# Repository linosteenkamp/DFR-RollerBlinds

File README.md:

# DFR-RollerBlinds

**ESP32-C6 stepper-driven Zigbee-router roller blind controller**

> *Photo placeholder — installed enclosure + motor + roller tube, to be added
> after bench verification.*

A Seeed XIAO ESP32C6 that drives a bipolar stepper (through a BIGTREETECH
TMC2209 and a 3D-printed 1:15 reduction) to raise and lower a roller blind,
in near silence thanks to the driver's StealthChop2 chopping, and presents a
standard **Window Covering** device (cluster 0x0102) to zigbee2mqtt / Home
Assistant. It joins the mesh as a **Zigbee Router** — mains-powered,
always-on, relays traffic and extends network range. A 3-key membrane keypad
(Up / Down / Fn) gives full local control and hosts a guided calibration
flow; firmware updates are delivered over the air through zigbee2mqtt.

## Features

- **Window Covering cluster (0x0102)** — full open/close, stop, and
  go-to-percentage, with live lift-position reporting during moves
- **Local keypad control** — tap for full travel, hold to jog, works even
  before calibration or with Zigbee down
- **Guided calibration** — hold Fn ~3 s, jog to the two limits, done; LED
  feedback at every step
- **Position Unknown recovery** — a power cut mid-move is detected and
  recovered with a lightweight one-mark Re-home instead of full recalibration
- **Motor Reversed** — per-unit installer setting (keypad chord or z2m),
  correcting for front-roll vs back-roll installs
- **Zigbee Router** — always-on radio, relays traffic and extends the mesh;
  built on the shared `esp-zb-common` library
- **Zigbee OTA** — CI-built images delivered through zigbee2mqtt with
  dual-slot bootloader rollback
- **Host-testable core** — position math, ramp planning, and keypad gesture
  classification are pure-C modules with a `native` unit-test suite

## Getting started

```bash
# Build & flash
pio run -e seeed_xiao_esp32c6_zigbee -t upload -t monitor

# Host unit tests
pio test -e native
```

Pairing, calibration, and OTA setup are in
[DEVELOPER_GUIDE.md](DEVELOPER_GUIDE.md).

> **Fitting a unit to a blind?** Follow the
> [per-blind install checklist](HARDWARE.md#installing-a-unit-per-blind-checklist).
> The fleet uses **two different motors**, and each needs its own Vref *and* its
> own motor cable — the cables are not interchangeable, and mismatching either
> one produces a stall that looks like a firmware or speed problem.

## Documentation

- **[HARDWARE.md](HARDWARE.md)** — BOM, power chain, TMC2209 wiring, Vref
  procedure, keypad/LED wiring, direction check, and the
  [per-blind install checklist](HARDWARE.md#installing-a-unit-per-blind-checklist)
- **[DEVELOPER_GUIDE.md](DEVELOPER_GUIDE.md)** — pairing, calibration
  walkthrough, bench checklist, OTA release flow
- **[CLAUDE.md](CLAUDE.md)** — architecture, module table, concurrency rule
- **[PARTITIONS.md](PARTITIONS.md)** — flash partition layout (dual-OTA)
- **[docs/superpowers/specs/2026-07-18-roller-blinds-design.md](docs/superpowers/specs/2026-07-18-roller-blinds-design.md)** — full design spec

## License

Provided as-is for educational and development purposes.

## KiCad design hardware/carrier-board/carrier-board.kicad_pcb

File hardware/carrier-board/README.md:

# Carrier board (rev A)

KiCad 10 project for the roller-blind controller's carrier board: the XIAO
ESP32C6 and BTT TMC2209 V1.3 plug into sockets, 24 V DC comes in on a screw
terminal, and an on-board AP64200 makes 5 V. The v2.4.x pin map is unchanged,
so the board needs no firmware release.

Planned and tracked on the wayfinder map
[PCBWay carrier board for the roller-blind controller](https://github.com/linosteenkamp/DFR-RollerBlinds/issues/1).
The part choices are justified in `docs/research/` (`buck-regulator.md`,
`input-protection.md`, `module-footprints.md`, `pcbway-kicad.md`).

| File | What it is |
|---|---|
| `carrier-board.kicad_sch` | The schematic: the source of truth. Edit it in the KiCad GUI. |
| `carrier-board.kicad_pcb` | The layout: 80 × 50 mm, 2 layers, routed. The source of truth for the board. |
| `carrier-board.kicad_dru` | PCBWay's published KiCad DRC rules (2-layer, 1 oz set), unchanged |
| `carrier-board.kicad_pro` | Project settings, including the net classes (see below) |
| `carrier.kicad_sym` (+ `sym-lib-table`) | Project symbols: the module sockets, AP64200, a DPAK-numbered P-FET, and the DNP module placeholders |
| `carrier.pretty/` (+ `fp-lib-table`) | Project footprints: tight-courtyard sockets for the TMC2209 (its DIAG row sits 2.54 mm from EN), plus no-silk copies of the test pad, L1 and J6 |
| `carrier-board-schematic.pdf` | Schematic plot for review |
| `fab/` | The PCBWay upload package and `export.sh`, which rebuilds it (see below) |
| `renders/` | `top.png`/`bottom.png` (3D) and `copper-t.png`/`copper-b.png` (tracks, without the pours), for review |

## Checks

```bash
kicad-cli sch erc --severity-all --exit-code-violations carrier-board.kicad_sch
kicad-cli pcb drc --severity-all --schematic-parity --exit-code-violations carrier-board.kicad_pcb
```

Rev A passes both at every severity. DRC finds 0 violations, 0 unconnected
items and 0 schematic-parity issues. The schematic's netlist was also checked
net by net against the intended connections: 37 named nets, plus 3
intentional no-connects (TMC2209 TX, CLK and VREF).

## How the schematic is drawn

Every connection goes through a **net label** on a short wire stub at the
pin. There are no long wires. So to find everything on a net, search for its
label.

The modules are not parts on this board. `U1` (XIAO) and `U2` (TMC2209) are
pinless DNP placeholders. The sockets they plug into, `J2`/`J3` (XIAO) and
`J4`/`J5`/`J6` (TMC2209), are real parts that get assembled. This is the
approach PCBWay's assembly guidance calls for (see `docs/research/pcbway-kicad.md`).

## How the layout was made

Placement follows the map's placement decision. The 24 V terminal and the
motor connector sit at the left end, with the TMC2209 beside them and turned
180° so its power column faces them. The buck is in the middle. The XIAO sits
at the right end with its USB-C at the top edge and its antenna end inboard,
over a copper-free keep-out. The keypad connector is at the right edge, and
the four corners have M3 holes. Reference designators are on the Fab
(assembly) layer, so the silkscreen carries only function labels.

It was routed by Freerouting 2.5.0, which needs **Java 25**:
`brew install openjdk@25`, then `/opt/homebrew/opt/openjdk@25/bin/java -jar …`.
The KiCad plugin's Java 21 can't run it.

**GND is routed as real traces**, not only through the pours. The two GND
pours were added after routing, then stitched together with vias: a grid of
them, one beside every SMD GND pad, and six under the AP64200's exposed pad.
The order matters. A board exported with its pours turns GND into a "plane",
which Freerouting doesn't route, and the top pour then breaks into islands
under the buck. Re-routing from scratch has to follow the same order: remove
the pours, export the DSN, route, import the SES, then re-add the pours and
the stitching.

Net classes and their track widths:

| Class | Nets | Width |
|---|---|---|
| Power | 24V_IN, 24V_F, +24V, VM | 1.0 mm |
| Motor | MOT_A1/A2/B1/B2 | 0.8 mm |
| Supply | +5V_BUCK, 5V_PRE, +5V, SW, +3V3 | 0.5 mm |
| Ground | GND | 0.5 mm, plus the pours |
| Default | signals | 0.25 mm |

Freerouting narrows a few segments where they meet fine-pitch pads: 7 Power
segments down to 0.6 mm, and some signal segments down to 0.19 mm. All are
above PCBWay's 0.127 mm minimum.

## The PCBWay package

`fab/export.sh` rebuilds everything in `fab/` from the KiCad files. It fails
unless ERC and DRC (with parity) are clean at every severity.

| File | Upload as |
|---|---|
| `carrier-board-revA-gerbers.zip` | The PCB file: Gerbers (X2, origin at the lower-left corner), Excellon drill in mm with PTH and NPTH split, and an IPC-D-356 netlist |
| `carrier-board-revA-bom.csv` | The BOM: one row per part, every designator spelled out, with the modules and J9 as DNP rows |
| `carrier-board-revA-centroid.csv` | Pick and place: top side only, SMD only, mm, from the same origin |
| `carrier-board-revA-assembly.pdf` | The assembly drawing. Designators are on the Fab layer, not the silkscreen, so this is where PCBWay finds them |

Order settings: 2 layers, FR-4 (TG150), 1.6 mm, 1 oz copper, 6/6 mil, 0.3 mm min hole, HASL lead-free, green
mask, white silk, 10 boards, all 10 assembled turnkey. Through-hole parts are
fitted too (C1, J1-J8; J9 is not fitted). Allow substitutes. The BOM's Note
column says which parts are generic and which must not change: L1 needs
Isat ≥ 4.5 A, C4/C5 must be 50 V X7R, and C7/C8 must be ≥ 16 V X7R.

Stock as of 2026-11-07 (Digi-Key unless stated): everything is in stock
except Phoenix 1715721, which Digi-Key expects around 30 Nov but RS,
element14 and TME have. D2 is an MMSZ5242BT1G, because BZT52C12 was on a
32-week lead time. L1 is a Bourns SRP7028A-100M (Isat 6 A), which fits the
footprint as laid out.

## Notes

- **PSUs stay at nominal 24 V** (the SMBJ24A TVS clamps above that). This is
  printed on the bottom silkscreen beside the input: "24 V NOMINAL - DO NOT TRIM PSU UP".

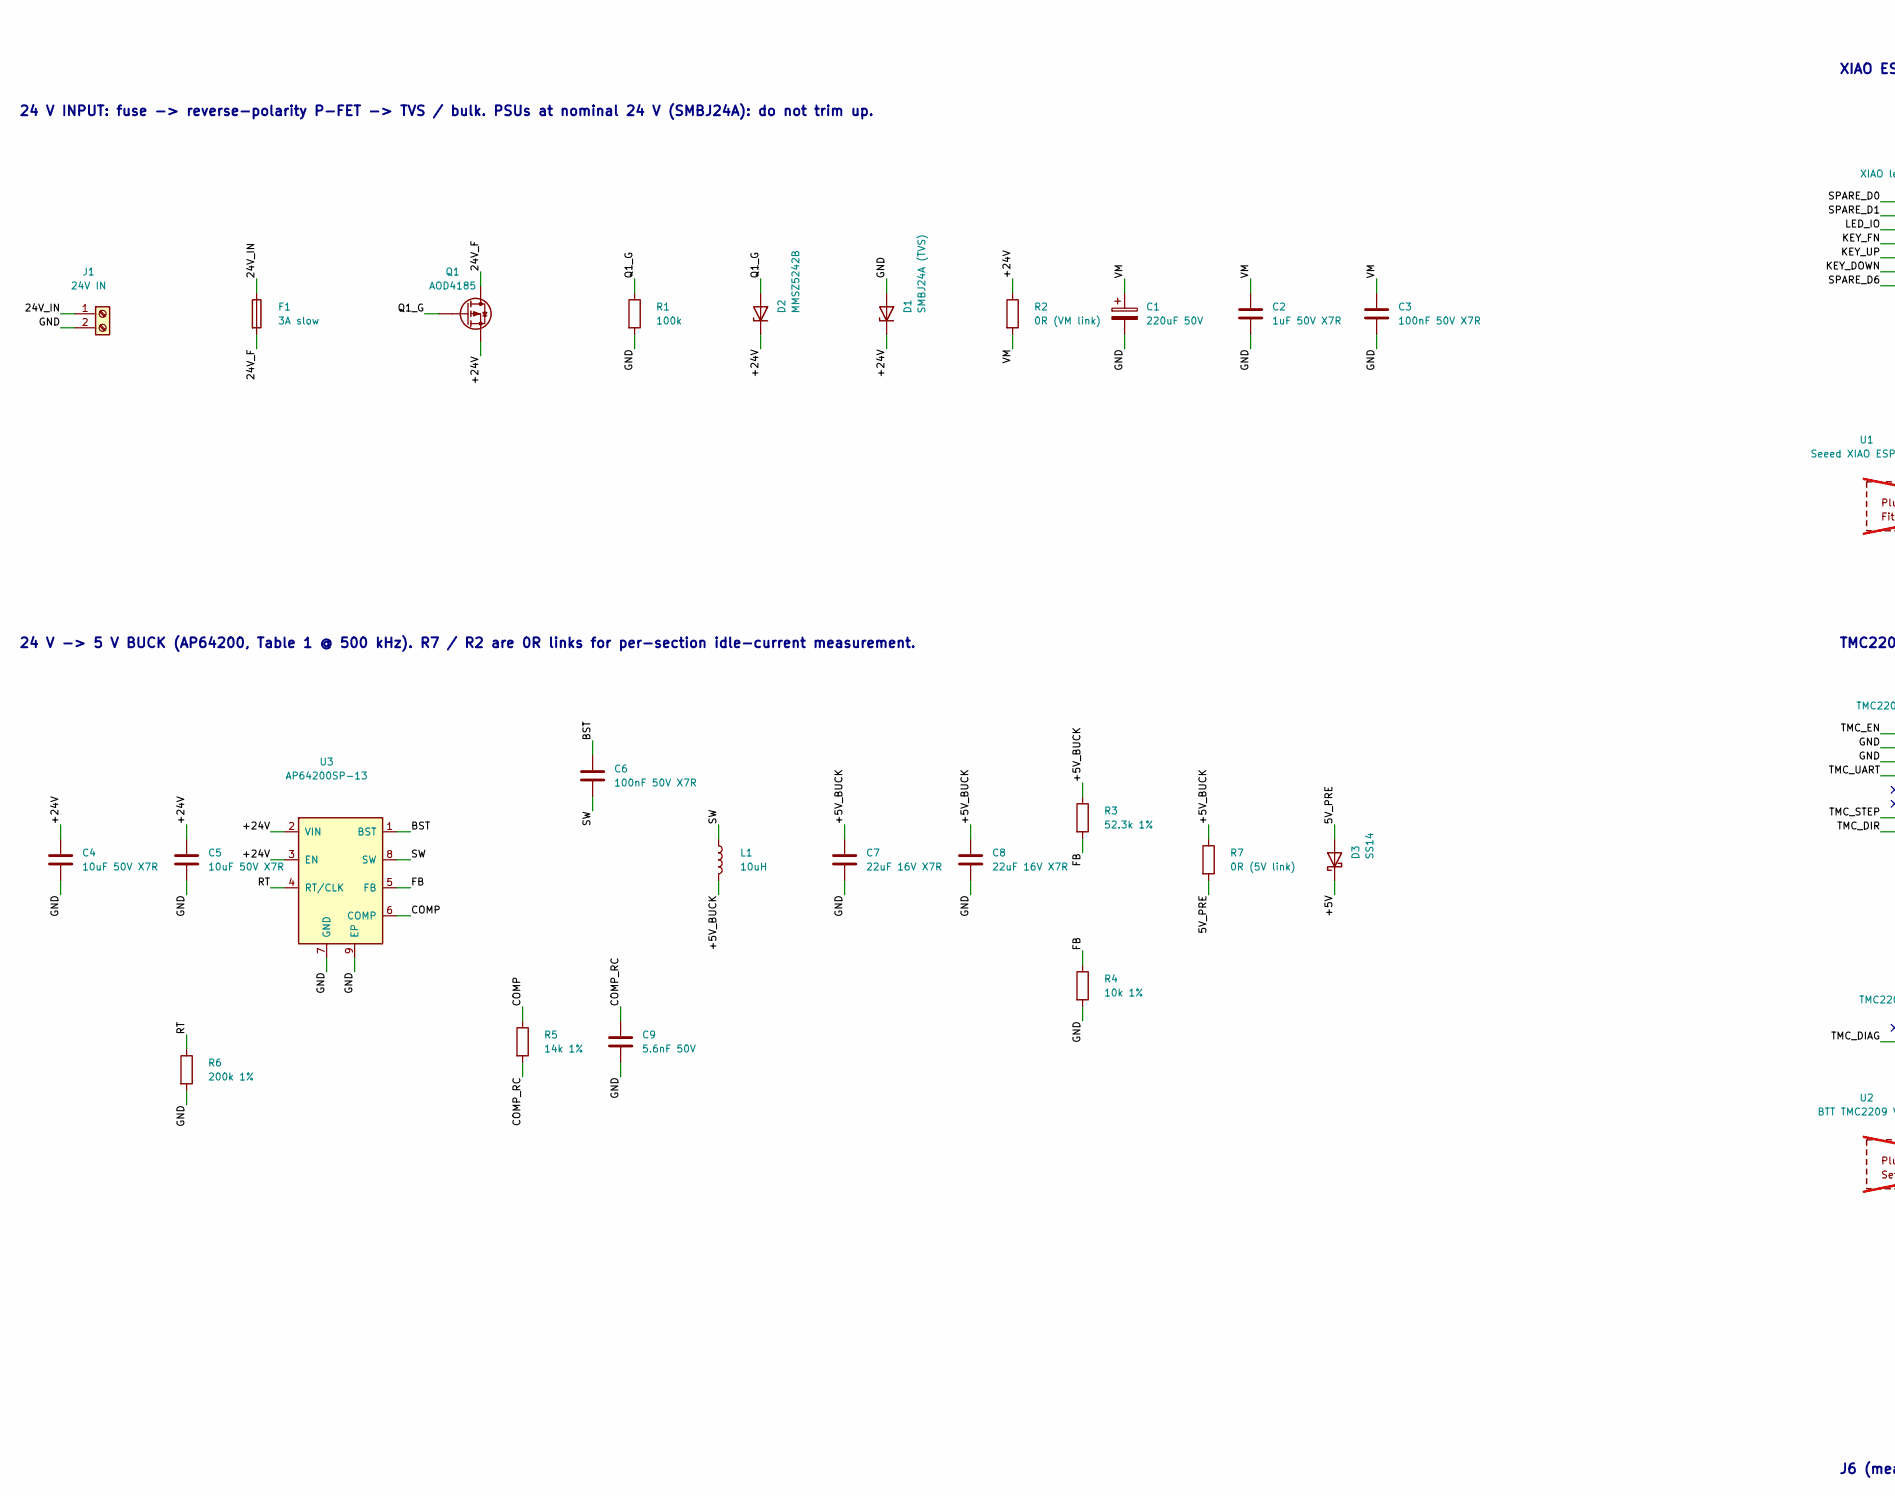
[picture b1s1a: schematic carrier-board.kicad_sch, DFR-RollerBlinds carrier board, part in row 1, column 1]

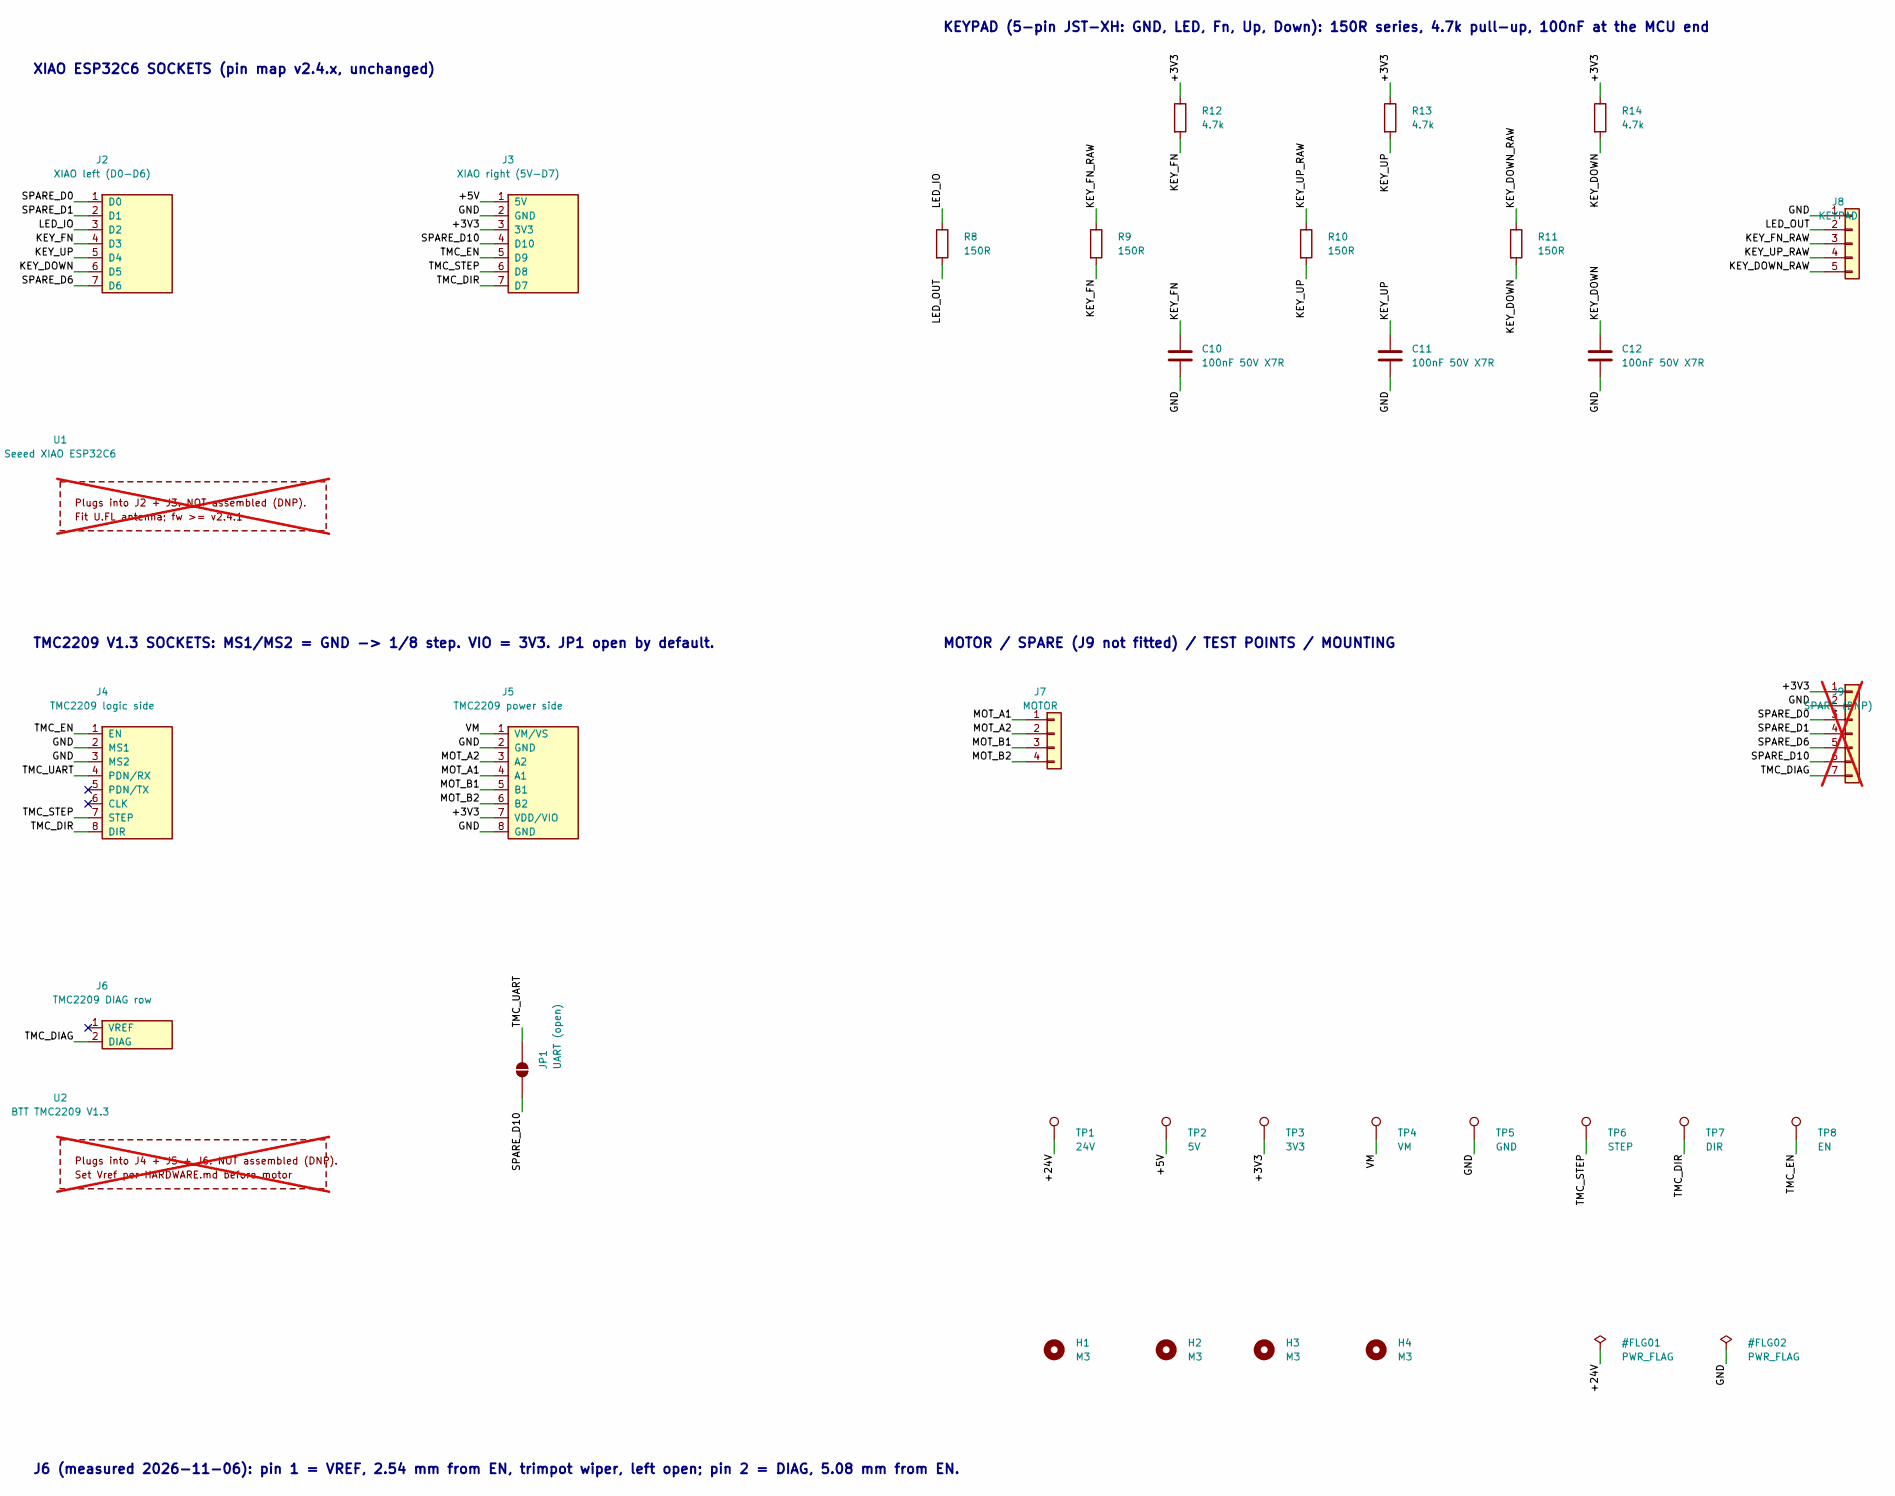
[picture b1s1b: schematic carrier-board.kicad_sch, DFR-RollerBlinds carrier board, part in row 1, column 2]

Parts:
C1: 220uF 50V; CP_Radial_D10.0mm_P5.00mm; MPN 50ZLH220MEFC10X16
C2: 1uF 50V X7R; C_0805_2012Metric
C3, C6, C10, C11, C12: 100nF 50V X7R; C_0603_1608Metric
C4, C5: 10uF 50V X7R; C_1206_3216Metric; MPN GRM31CR71H106KA12L
C7, C8: 22uF 16V X7R; C_1206_3216Metric; MPN CL31B226KOHNNNE
C9: 5.6nF 50V; C_0603_1608Metric
D1: SMBJ24A (TVS); D_SMB; MPN SMBJ24A-13-F
D2: MMSZ5242B; D_SOD-123; MPN MMSZ5242BT1G
D3: SS14; D_SMA; MPN SS14-E3/61T
F1: 3A slow; Fuse_1206_3216Metric; MPN SF-1206S300-2
H1, H2, H3, H4: M3; MountingHole_3.2mm_M3
J1: 24V IN; TerminalBlock_Phoenix_MKDS-1,5-2-5.08_1x02_P5.08mm_Horizont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; MPN 1715721
J2: XIAO left (D0-D6); PinSocket_1x07_P2.54mm_Vertical; MPN PPTC071LFBN-RC
J3: XIAO right (5V-D7); PinSocket_1x07_P2.54mm_Vertical; MPN PPTC071LFBN-RC
J4: TMC2209 logic side; PinSocket_1x08_P2.54mm_Vertical_Tight; MPN PPTC081LFBN-RC
J5: TMC2209 power side; PinSocket_1x08_P2.54mm_Vertical_Tight; MPN PPTC081LFBN-RC
J6: TMC2209 DIAG row; PinSocket_1x02_P2.54mm_Vertical_Tight_NoSilk; MPN PPTC021LFBN-RC
J7: MOTOR; JST_XH_S4B-XH-A_1x04_P2.50mm_Horizontal; MPN S4B-XH-A(LF)(SN)
J8: KEYPAD; JST_XH_S5B-XH-A_1x05_P2.50mm_Horizontal; MPN S5B-XH-A(LF)(SN)
J9: SPARE (DNP); PinHeader_1x07_P2.54mm_Vertical; not fitted
JP1: UART (open); SolderJumper-2_P1.3mm_Open_RoundedPad1.0x1.5mm
L1: 10uH; L_7.3x6.6mm_NoSilk; MPN SRP7028A-100M
Q1: AOD4185; TO-252-2; MPN AOD4185
R1: 100k; R_0603_1608Metric
R2: 0R (VM link); R_1206_3216Metric
R3: 52.3k 1%; R_0603_1608Metric
R4: 10k 1%; R_0603_1608Metric
R5: 14k 1%; R_0603_1608Metric
R6: 200k 1%; R_0603_1608Metric
R7: 0R (5V link); R_1206_3216Metric
R8, R9, R10, R11: 150R; R_0603_1608Metric
R12, R13, R14: 4.7k; R_0603_1608Metric
TP1: 24V; TestPoint_THTPad_D1.5mm_Drill0.7mm_NoSilk
TP2: 5V; TestPoint_THTPad_D1.5mm_Drill0.7mm_NoSilk
TP3: 3V3; TestPoint_THTPad_D1.5mm_Drill0.7mm_NoSilk
TP4: VM; TestPoint_THTPad_D1.5mm_Drill0.7mm_NoSilk
TP5: GND; TestPoint_THTPad_D1.5mm_Drill0.7mm_NoSilk
TP6: STEP; TestPoint_THTPad_D1.5mm_Drill0.7mm_NoSilk
TP7: DIR; TestPoint_THTPad_D1.5mm_Drill0.7mm_NoSilk
TP8: EN; TestPoint_THTPad_D1.5mm_Drill0.7mm_NoSilk
U1: Seeed XIAO ESP32C6; not fitted
U2: BTT TMC2209 V1.3; not fitted
U3: AP64200SP-13; SOIC-8-1EP_3.9x4.9mm_P1.27mm_EP2.62x3.51mm; MPN AP64200SP-13

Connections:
/5V_PRE: D3.2 (A), R7.2
/24V_F: F1.2, Q1.2 (D)
/24V_IN: F1.1, J1.1
/+3V3: J3.3 (3V3), J5.7 (VDD/VIO), J9.1, R12.1, R13.1, R14.1, TP3.1
/+5V: D3.1 (K), J3.1 (5V), TP2.1
/+5V_BUCK: C7.1, C8.1, L1.2, R3.1, R7.1
/+24V: C4.1, C5.1, D1.1 (K), D2.1 (K), Q1.3 (S), R2.1, TP1.1, U3.2 (VIN), U3.3 (EN)
/BST: C6.1, U3.1 (BST)
/COMP: R5.1, U3.6 (COMP)
/COMP_RC: C9.1, R5.2
/FB: R3.2, R4.1, U3.5 (FB)
/GND: C1.2, C2.2, C3.2, C4.2, C5.2, C7.2, C8.2, C9.2, C10.2, C11.2, C12.2, D1.2 (A), J1.2, J3.2 (GND), J4.2 (MS1), J4.3 (MS2), J5.2 (GND), J5.8 (GND), J8.1, J9.2, R1.2, R4.2, R6.2, TP5.1, U3.7 (GND), U3.9 (EP)
/KEY_DOWN: C12.1, J2.6 (D5), R11.2, R14.2
/KEY_DOWN_RAW: J8.5, R11.1
/KEY_FN: C10.1, J2.4 (D3), R9.2, R12.2
/KEY_FN_RAW: J8.3, R9.1
/KEY_UP: C11.1, J2.5 (D4), R10.2, R13.2
/KEY_UP_RAW: J8.4, R10.1
/LED_IO: J2.3 (D2), R8.1
/LED_OUT: J8.2, R8.2
/MOT_A1: J5.4 (A1), J7.1
/MOT_A2: J5.3 (A2), J7.2
/MOT_B1: J5.5 (B1), J7.3
/MOT_B2: J5.6 (B2), J7.4
/Q1_G: D2.2 (A), Q1.1 (G), R1.1
/RT: R6.1, U3.4 (RT/CLK)
/SPARE_D0: J2.1 (D0), J9.3
/SPARE_D1: J2.2 (D1), J9.4
/SPARE_D6: J2.7 (D6), J9.5
/SPARE_D10: J3.4 (D10), J9.6, JP1.1 (A)
/SW: C6.2, L1.1, U3.8 (SW)
/TMC_DIAG: J6.2 (DIAG), J9.7
/TMC_DIR: J3.7 (D7), J4.8 (DIR), TP7.1
/TMC_EN: J3.5 (D9), J4.1 (EN), TP8.1
/TMC_STEP: J3.6 (D8), J4.7 (STEP), TP6.1
/TMC_UART: J4.4 (PDN/RX), JP1.2 (B)
/VM: C1.1, C2.1, C3.1, J5.1 (VM/VS), R2.2, TP4.1

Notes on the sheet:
24 V INPUT: fuse -> reverse-polarity P-FET -> TVS / bulk. PSUs at nominal 24 V (SMBJ24A): do not trim up.
24 V -> 5 V BUCK (AP64200, Table 1 @ 500 kHz). R7 / R2 are 0R links for per-section idle-current measurement.
XIAO ESP32C6 SOCKETS (pin map v2.4.x, unchanged)
TMC2209 V1.3 SOCKETS: MS1/MS2 = GND -> 1/8 step. VIO = 3V3. JP1 open by default.
KEYPAD (5-pin JST-XH: GND, LED, Fn, Up, Down): 150R series, 4.7k pull-up, 100nF at the MCU end
MOTOR / SPARE (J9 not fitted) / TEST POINTS / MOUNTING
J6 (measured 2026-11-06): pin 1 = VREF, 2.54 mm from EN, trimpot wiper, left open; pin 2 = DIAG, 5.08 mm from EN.

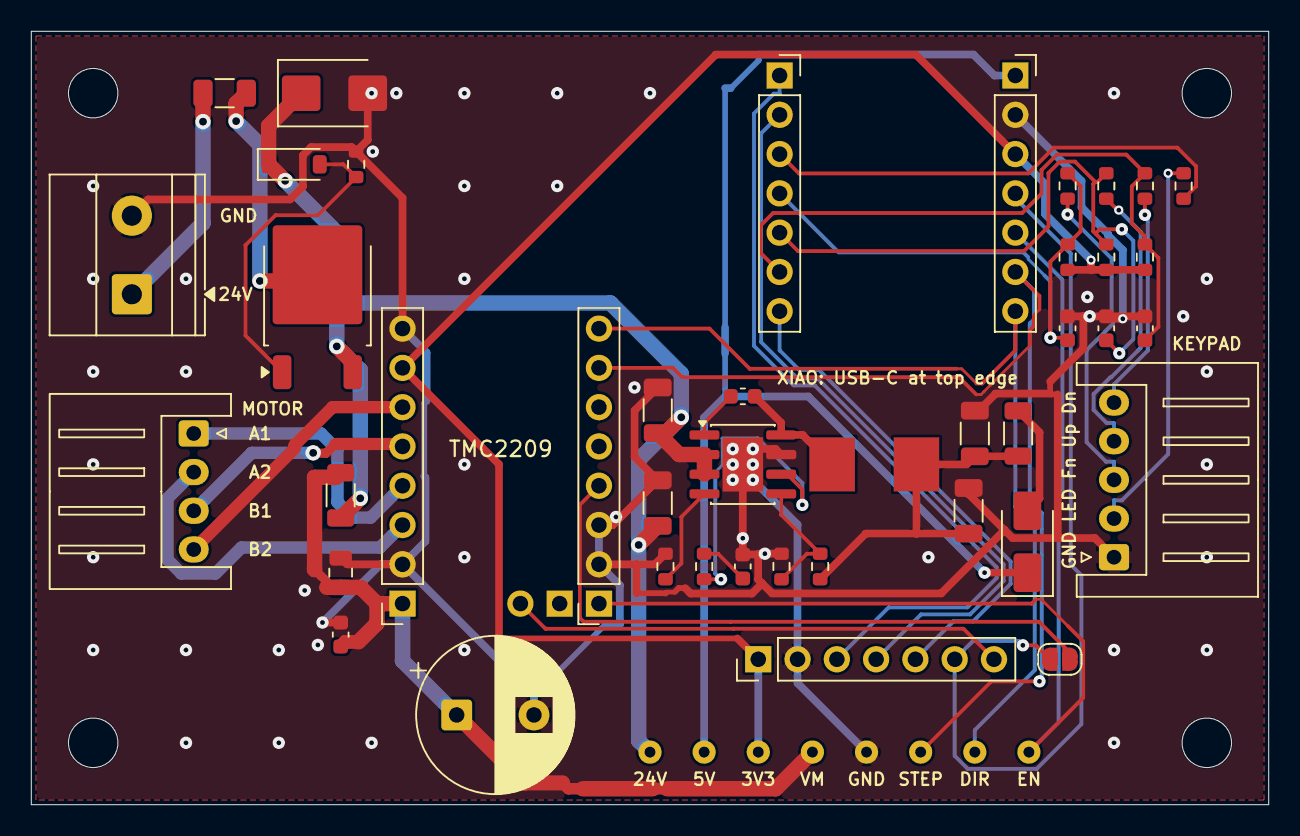
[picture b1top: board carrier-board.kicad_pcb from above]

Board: 2 copper layers, 80.0 x 50.0 mm, 55 parts (0 on the bottom side), 37 nets.

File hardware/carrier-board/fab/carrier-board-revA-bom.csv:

"Designator","Quantity","Value","Package","Type","Manufacturer","Manufacturer Part Number","Note","DNP"
"C1","1","220uF 50V","Radial D10 P5.0","THT","Rubycon","50ZLH220MEFC10X16","Polarised: + pad marked; low-ESR 50 V, D10 P5 equivalent OK",""
"C2","1","1uF 50V X7R","0805","SMD","","","Generic, substitute OK",""
"C3,C6,C10,C11,C12","5","100nF 50V X7R","0603","SMD","","","Generic, substitute OK",""
"C4,C5","2","10uF 50V X7R","1206","SMD","Murata","GRM31CR71H106KA12L","Must be 50 V X7R",""
"C7,C8","2","22uF 16V X7R","1206","SMD","Samsung","CL31B226KOHNNNE","Must be >= 16 V X7R",""
"C9","1","5.6nF 50V","0603","SMD","","","Generic, substitute OK",""
"D1","1","SMBJ24A (TVS)","SMB","SMD","Diodes Inc","SMBJ24A-13-F","",""
"D2","1","MMSZ5242B","SOD-123","SMD","onsemi","MMSZ5242BT1G","12 V zener; BZT52C12 equivalent OK",""
"D3","1","SS14","SMA","SMD","Vishay","SS14-E3/61T","",""
"F1","1","3A slow","1206","SMD","Bourns","SF-1206S300-2","",""
"J1","1","24V IN","5.08mm 2-pos","THT","Phoenix Contact","1715721","Equivalent 5.08 mm 2-pole horizontal-entry terminal OK",""
"J2","1","XIAO left (D0-D6)","1x07 2.54 female","THT","Sullins","PPTC071LFBN-RC","8.5 mm female socket; fit flush and square",""
"J3","1","XIAO right (5V-D7)","1x07 2.54 female","THT","Sullins","PPTC071LFBN-RC","8.5 mm female socket; fit flush and square",""
"J4","1","TMC2209 logic side","1x08 2.54 female","THT","Sullins","PPTC081LFBN-RC","8.5 mm female socket; fit flush and square",""
"J5","1","TMC2209 power side","1x08 2.54 female","THT","Sullins","PPTC081LFBN-RC","8.5 mm female socket; fit flush and square",""
"J6","1","TMC2209 DIAG row","1x02 2.54 female","THT","Sullins","PPTC021LFBN-RC","8.5 mm female socket; fit flush and square",""
"J7","1","MOTOR","XH 4-pin side entry","THT","JST","S4B-XH-A(LF)(SN)","",""
"J8","1","KEYPAD","XH 5-pin side entry","THT","JST","S5B-XH-A(LF)(SN)","",""
"J9","1","SPARE (DNP)","1x07 2.54 male","THT","","","Do not fit","DNP"
"L1","1","10uH","7x7 shielded","SMD","Bourns","SRP7028A-100M","Isat >= 4.5 A required; no substitute without approval",""
"Q1","1","AOD4185","TO-252","SMD","Alpha & Omega","AOD4185","",""
"R1","1","100k","0603","SMD","","","Generic, substitute OK",""
"R2","1","0R (VM link)","1206","SMD","","","0 ohm jumper, >= 1 A; generic, substitute OK",""
"R3","1","52.3k 1%","0603","SMD","","","1% thick film; generic, substitute OK",""
"R4","1","10k 1%","0603","SMD","","","1% thick film; generic, substitute OK",""
"R5","1","14k 1%","0603","SMD","","","1% thick film; generic, substitute OK",""
"R6","1","200k 1%","0603","SMD","","","1% thick film; generic, substitute OK",""
"R7","1","0R (5V link)","1206","SMD","","","0 ohm jumper, >= 1 A; generic, substitute OK",""
"R8,R9,R10,R11","4","150R","0603","SMD","","","Generic, substitute OK",""
"R12,R13,R14","3","4.7k","0603","SMD","","","Generic, substitute OK",""
"U1","1","Seeed XIAO ESP32C6","","","","","Plug-in module, fitted by customer: do not buy or fit","DNP"
"U2","1","BTT TMC2209 V1.3","","","","","Plug-in module, fitted by customer: do not buy or fit","DNP"
"U3","1","AP64200SP-13","SO-8EP","SMD","Diodes Inc","AP64200SP-13","",""

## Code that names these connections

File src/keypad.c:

/**
 * @file keypad.c
 * @brief 5 ms polling of the membrane keys (active-low, internal pull-ups).
 *        key_filter integrator -> keypad_logic classifier -> app queue.
 *        The integrator is what makes this safe on an installed unit: the
 *        harness runs beside the stepper drive, and the previous change
 *        detector turned a single coupled glitch into a full travel.
 */
#include "keypad.h"
#include "keypad_logic.h"
#include "app_event.h"
#include "key_filter.h"
#include "trace.h"

#include "driver/gpio.h"
#include "esp_timer.h"
#include "esp_log.h"

#define POLL_MS        5
#define FILTER_SAMPLES 12   /* net 12-sample excess to flip: 60 ms if the level
                               is cleanly settled, longer on a rattling line */
_Static_assert(FILTER_SAMPLES > 0, "integrator needs a non-zero window");
#define HOLD_MS   400
#define LONG_MS   3000
#define RESET_MS  5000

/* ---- swallowed-press telemetry ----
 *
 * A press the integrator rejects leaves no trace anywhere else: no event
 * reaches the dispatcher, so every other trace code is silent and the keypad
 * is indistinguishable from a dead one. These record the near-misses.
 *
 * The depth threshold is what separates the two populations. An excursion
 * shallower than half the window is line noise being correctly rejected —
 * the thing the integrator was added to do — and tracing it would spend the
 * ring on a non-event. Half the window or deeper is a press that nearly made
 * it, which is the interesting case.
 *
 * Coalescing is not tidiness, it is what keeps the ring readable. A line
 * producing swallowed presses is by definition noisy, and one record per
 * excursion could wrap all 256 entries in well under a second, taking every
 * MOVE record with it — destroying the context that makes the dump worth
 * reading. One record per key per second instead, carrying the deepest
 * excursion of the window and how many there were.
 *
 * Every abandoned excursion counts, shallow ones included. An earlier version
 * ignored anything under half the window as "obviously noise" — but that is
 * the judgement the data is supposed to make, and a marginal contact that
 * barely moves the line looks exactly like noise while being a real press.
 * Coalescing already bounds the cost, so the threshold bought nothing and
 * could hide the case it was added to find. */
#define SWALLOW_WINDOW_MS 1000

/* Heartbeat. 60 s suits a session of a couple of hours: 120 records against
 * 256 slots, leaving room for events while sampling the line levels often
 * enough to correlate them with motor activity. For an unattended overnight
 * run raise this — at 60 s, eight hours of heartbeats alone wrap the ring
 * nearly twice and erase whatever the soak was left running to catch. */
#define ALIVE_PERIOD_MS   60000

static const char *TAG = "KEYPAD";

static int           s_gpio[KEY_COUNT];
static key_filter_t  s_filt[KEY_COUNT];
static kp_state_t    s_kp;
static QueueHandle_t s_queue;

static uint32_t s_swallow_t[KEY_COUNT];   /* window opened at */
static uint16_t s_swallow_n[KEY_COUNT];   /* near-misses in the window */
static uint8_t  s_swallow_d[KEY_COUNT];   /* deepest of them */

static int32_t  s_latch_a = -1, s_latch_b = -1;  /* last traced latch state */
static uint32_t s_alive_t;                /* last heartbeat */
static uint32_t s_alive_polls;            /* polls since it */

/* Packed for the dump, not for the code: see TRC_KEY_LATCH in trace.h. */
static void trace_latches(void)
{
    int32_t a = (s_kp.down[KEY_UP]   ? 1 << 0 : 0) |
                (s_kp.down[KEY_DOWN] ? 1 << 1 : 0) |
                (s_kp.down[KEY_FN]   ? 1 << 2 : 0) |
                (s_kp.holding[KEY_UP]   ? 1 << 4 : 0) |
                (s_kp.holding[KEY_DOWN] ? 1 << 5 : 0);
    /* Bits 0 and 1 held in_chord and in_reset, the two suppression latches
     * that could outlive their gesture and strand the keypad. They are gone,
     * and the bit positions stay reserved so a dump written by older firmware
     * still decodes: b=1 or b=3 in an old dump is the latch fault. */
    int32_t b = (s_kp.long_fired ? 1 << 2 : 0) |
                (s_kp.reset_fired ? 1 << 3 : 0);

    /* Only transitions: the flags are steady for whole seconds at a time, and
     * a record per poll would bury everything else 200 times a second. */
    if (a != s_latch_a || b != s_latch_b) {
        s_latch_a = a;
        s_latch_b = b;
        TRACE(TRC_KEY_LATCH, a, b);
    }
}

bool keypad_key_held(key_id_t key)
{
    return key_filter_level(&s_filt[key]) == 0;   /* active-low */
}

static void post_kp(kp_event_t e)
{
    if (e.type == KP_EVT_NONE) return;
    app_event_t ev = { .type = APP_EVT_KEYPAD, .kp = e };
    if (xQueueSend(s_queue, &ev, 0) != pdTRUE) {
        /* Dropped. A dropped HOLD_END is caught by the dispatcher's dead-man
         * check against keypad_key_held(); this task never touches motion. */
        TRACE(TRC_QUEUE_FULL, e.type, 0);
        ESP_LOGE(TAG, "queue full, dropped kp event type=%d", e.type);
    }
}

static void poll_cb(void *arg)
{
    (void)arg;
    uint32_t now = (uint32_t)(esp_timer_get_time() / 1000);
    for (int k = 0; k < KEY_COUNT; k++) {
        if (key_filter_sample(&s_filt[k], gpio_get_level(s_gpio[k]))) {
            /* active-low: 0 = pressed. Read the debounced output rather than
             * the raw sample — they agree today, but the filter owns the
             * truth and a future change to the rail logic should not have to
             * know that the caller was relying on them matching. */
            bool pressed = key_filter_level(&s_filt[k]) == 0;

            /* A ragged edge is slow, and the classifier reads TAP vs HOLD off
             * the interval between two of them — so an edge slower than its
             * partner moves that decision without anything downstream being
             * able to tell. Silent on a clean line: only the late ones cost a
             * record. */
            uint16_t edge = key_filter_traverse(&s_filt[k]);
            if (edge > FILTER_SAMPLES) {
                TRACE(TRC_KEY_EDGE, k | (pressed ? 0x100 : 0), edge);
            }

            post_kp(kp_on_change(&s_kp, (key_id_t)k, pressed, now));
        }

        uint8_t depth = key_filter_take_swallowed(&s_filt[k]);
        if (depth > 0) {
            if (s_swallow_n[k] < UINT16_MAX) s_swallow_n[k]++;
            if (depth > s_swallow_d[k])      s_swallow_d[k] = depth;
        }
        if (s_swallow_n[k] &&
            (uint32_t)(now - s_swallow_t[k]) >= SWALLOW_WINDOW_MS) {
            TRACE(TRC_KEY_SWALLOWED, k,
                  s_swallow_d[k] | ((int32_t)s_swallow_n[k] << 16));
            s_swallow_t[k] = now;
            s_swallow_n[k] = 0;
            s_swallow_d[k] = 0;
        }
    }
    post_kp(kp_on_tick(&s_kp, now));

    /* After both classifier entry points, so a latch that a tick set or a
     * change cleared is recorded in the same poll it moved. */
    trace_latches();

    s_alive_polls++;
    if ((uint32_t)(now - s_alive_t) >= ALIVE_PERIOD_MS) {
        int32_t levels = 0;
        for (int k = 0; k < KEY_COUNT; k++) {
            levels |= (gpio_get_level(s_gpio[k])     ? 1 : 0) << k;
            levels |= (key_filter_level(&s_filt[k])  ? 1 : 0) << (k + 4);
        }
        TRACE(TRC_KEY_ALIVE, (int32_t)s_alive_polls, levels);
        s_alive_t     = now;
        s_alive_polls = 0;
    }
}

esp_err_t keypad_init(int gpio_up, int gpio_down, int gpio_fn, QueueHandle_t q)
{
    s_gpio[KEY_UP] = gpio_up;
    s_gpio[KEY_DOWN] = gpio_down;
    s_gpio[KEY_FN] = gpio_fn;
    s_queue = q;

    gpio_config_t io = {
        .pin_bit_mask = (1ULL << gpio_up) | (1ULL << gpio_down) | (1ULL << gpio_fn),
        .mode = GPIO_MODE_INPUT,
        .pull_up_en = GPIO_PULLUP_ENABLE,
    };
    esp_err_t err = gpio_config(&io);
    if (err != ESP_OK) return err;

    /* No GPIO glitch filter on the key pins. The C6's flex glitch filter was
     * enabled here until 2026-09-26, when a bench A/B on a fresh board proved
     * it latching a released key "pressed" while the motor ran: the pin
     * measured 3.3 V, the firmware read it low for 18 s, and the jog never
     * stopped. With only the filter removed, 30 of 30 jogs stopped on
     * release. The RC front end and the key_filter integrator reject noise. */

    for (int k = 0; k < KEY_COUNT; k++) {
        key_filter_init(&s_filt[k], FILTER_SAMPLES, gpio_get_level(s_gpio[k]));
    }
    kp_init(&s_kp, HOLD_MS, LONG_MS, RESET_MS);

    static esp_timer_handle_t timer;
    const esp_timer_create_args_t targs = { .callback = poll_cb, .name = "keypad" };
    err = esp_timer_create(&targs, &timer);
    if (err != ESP_OK) return err;
    return esp_timer_start_periodic(timer, POLL_MS * 1000);
}
